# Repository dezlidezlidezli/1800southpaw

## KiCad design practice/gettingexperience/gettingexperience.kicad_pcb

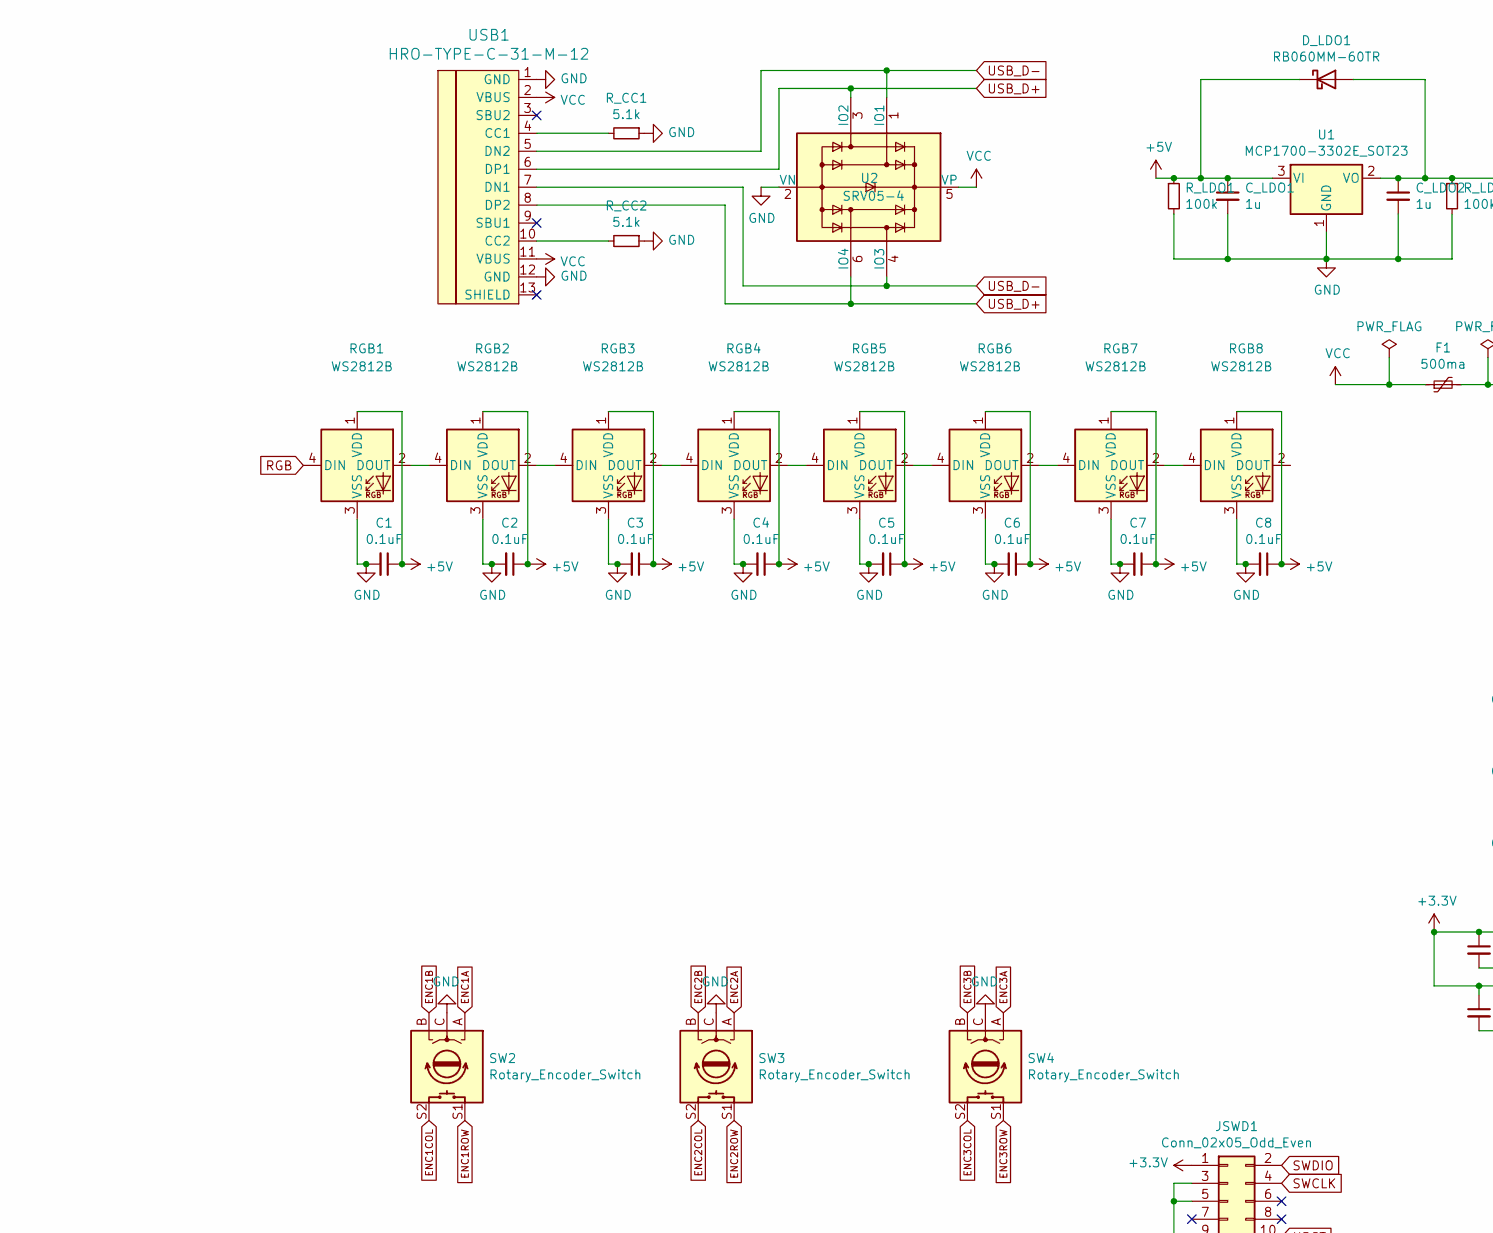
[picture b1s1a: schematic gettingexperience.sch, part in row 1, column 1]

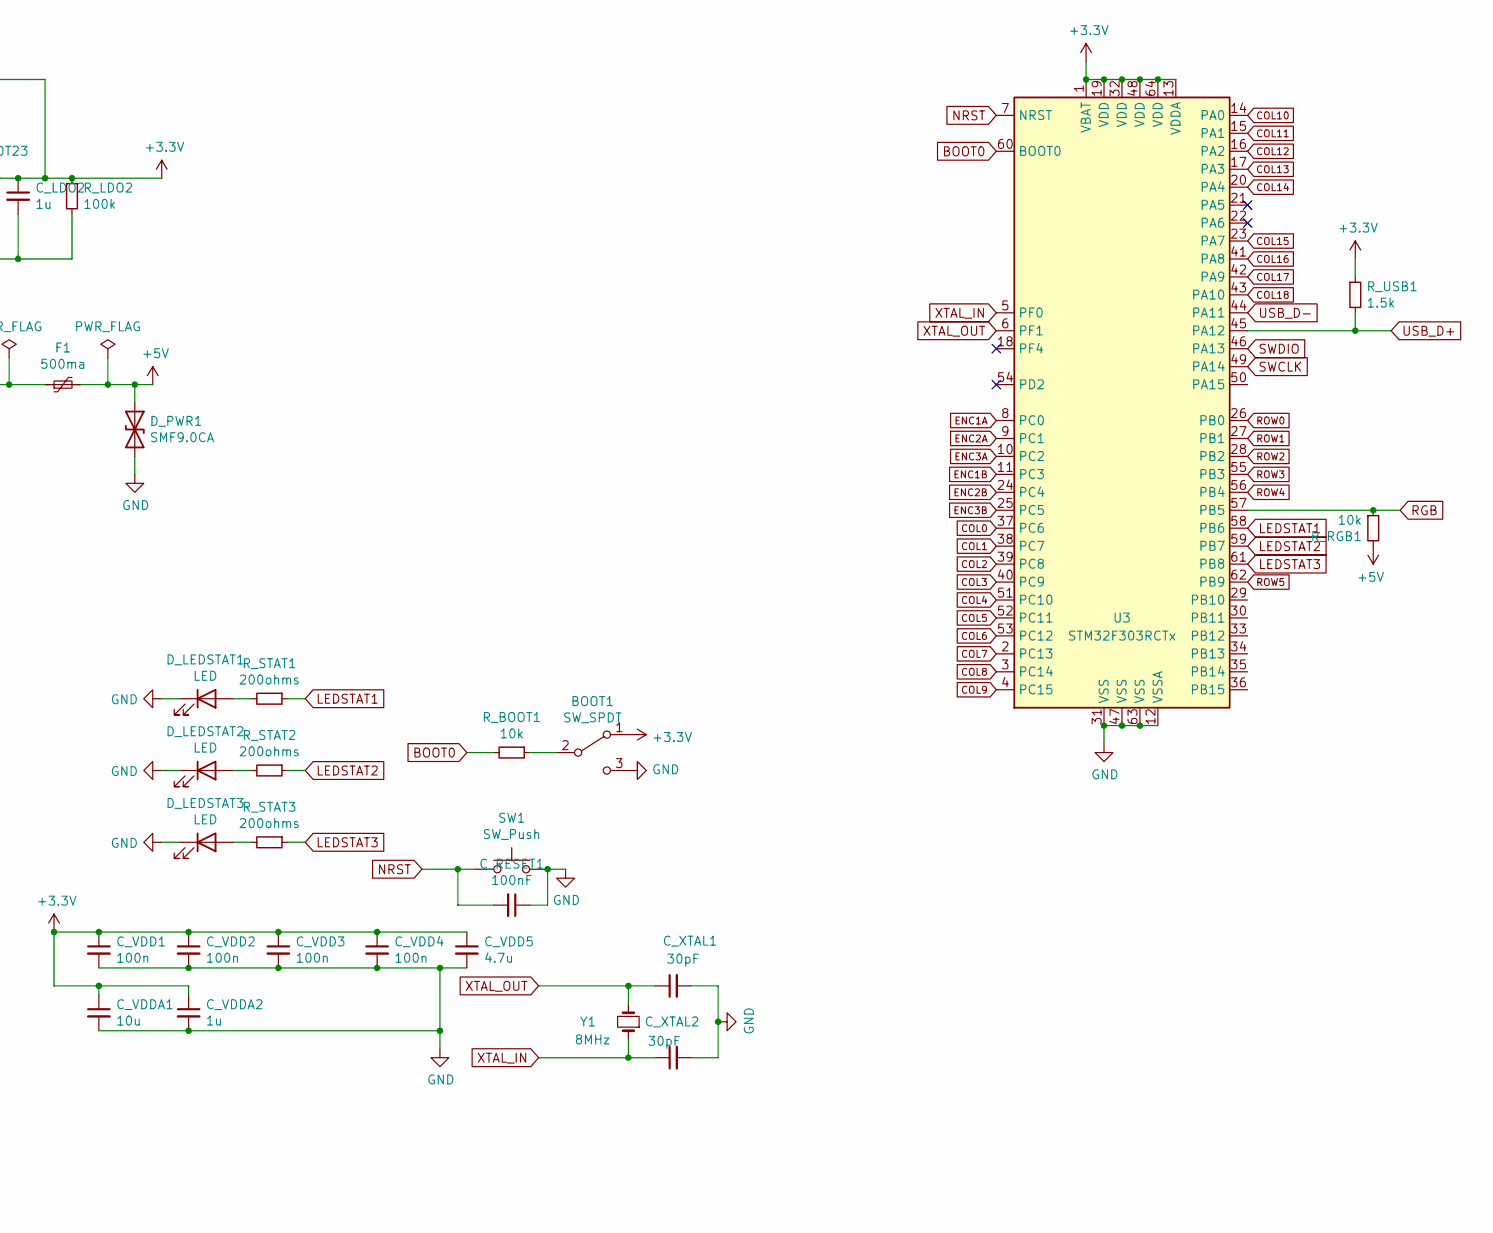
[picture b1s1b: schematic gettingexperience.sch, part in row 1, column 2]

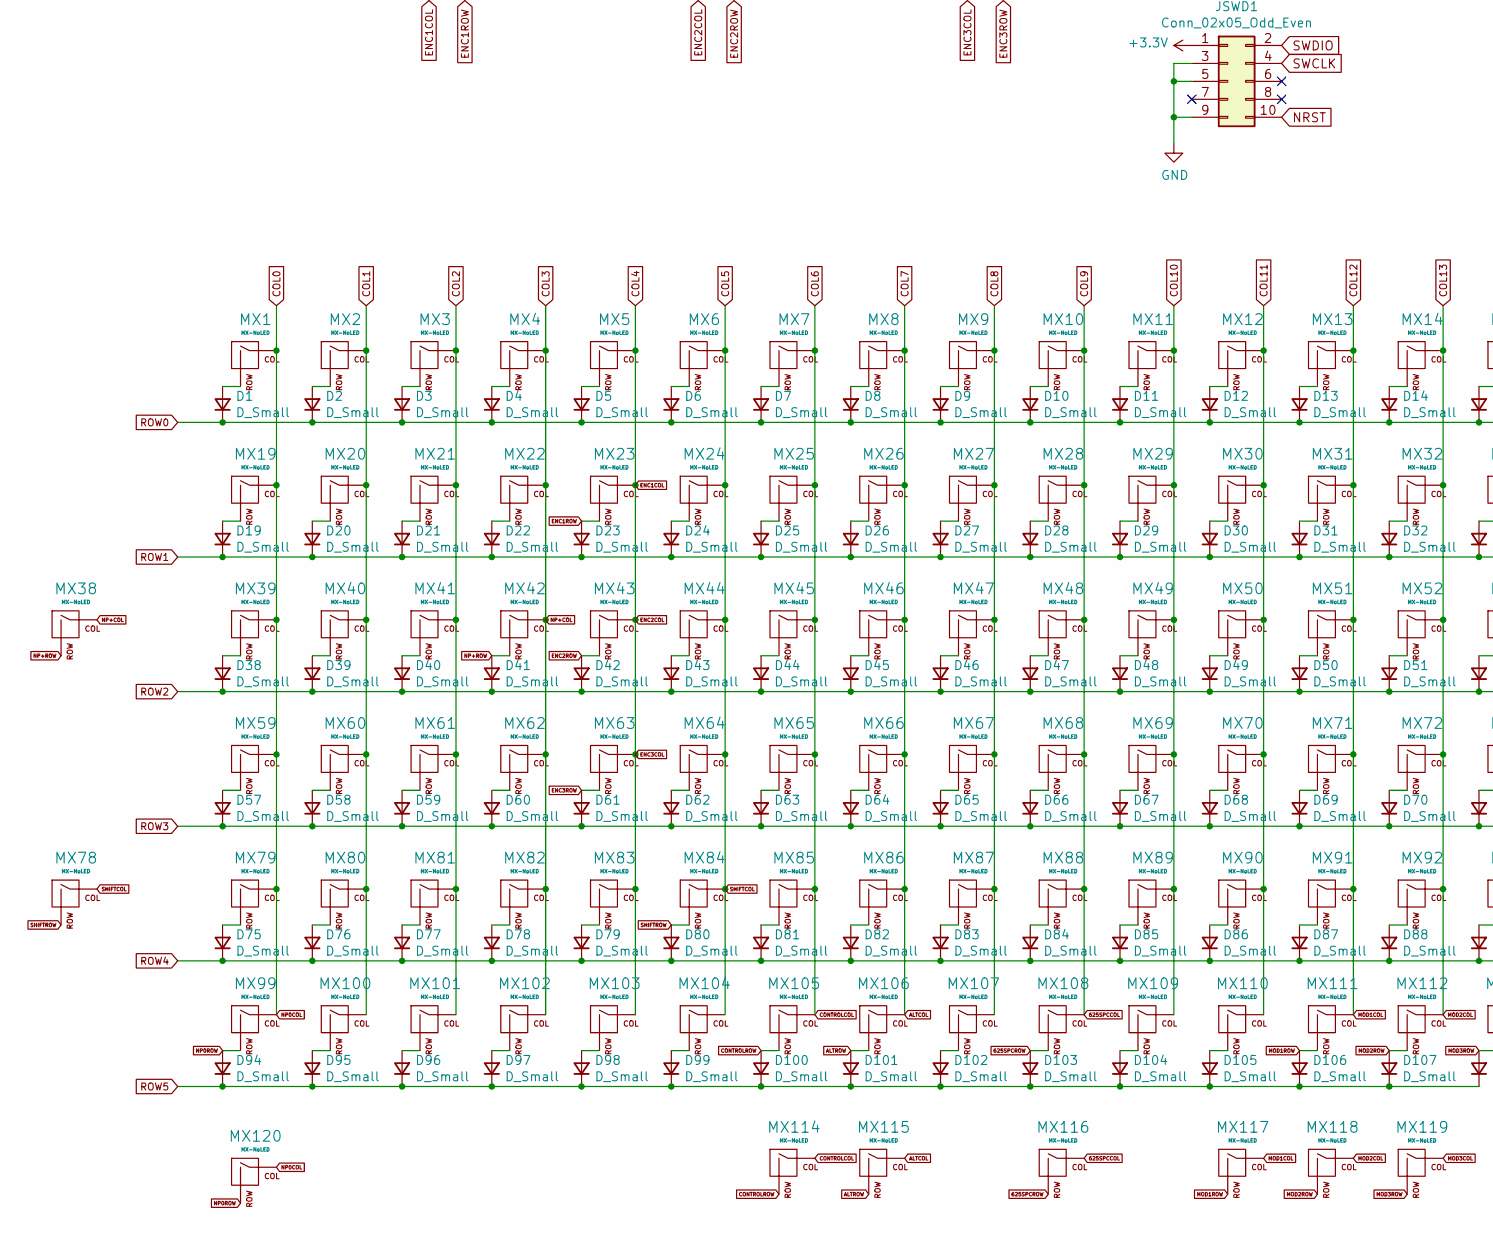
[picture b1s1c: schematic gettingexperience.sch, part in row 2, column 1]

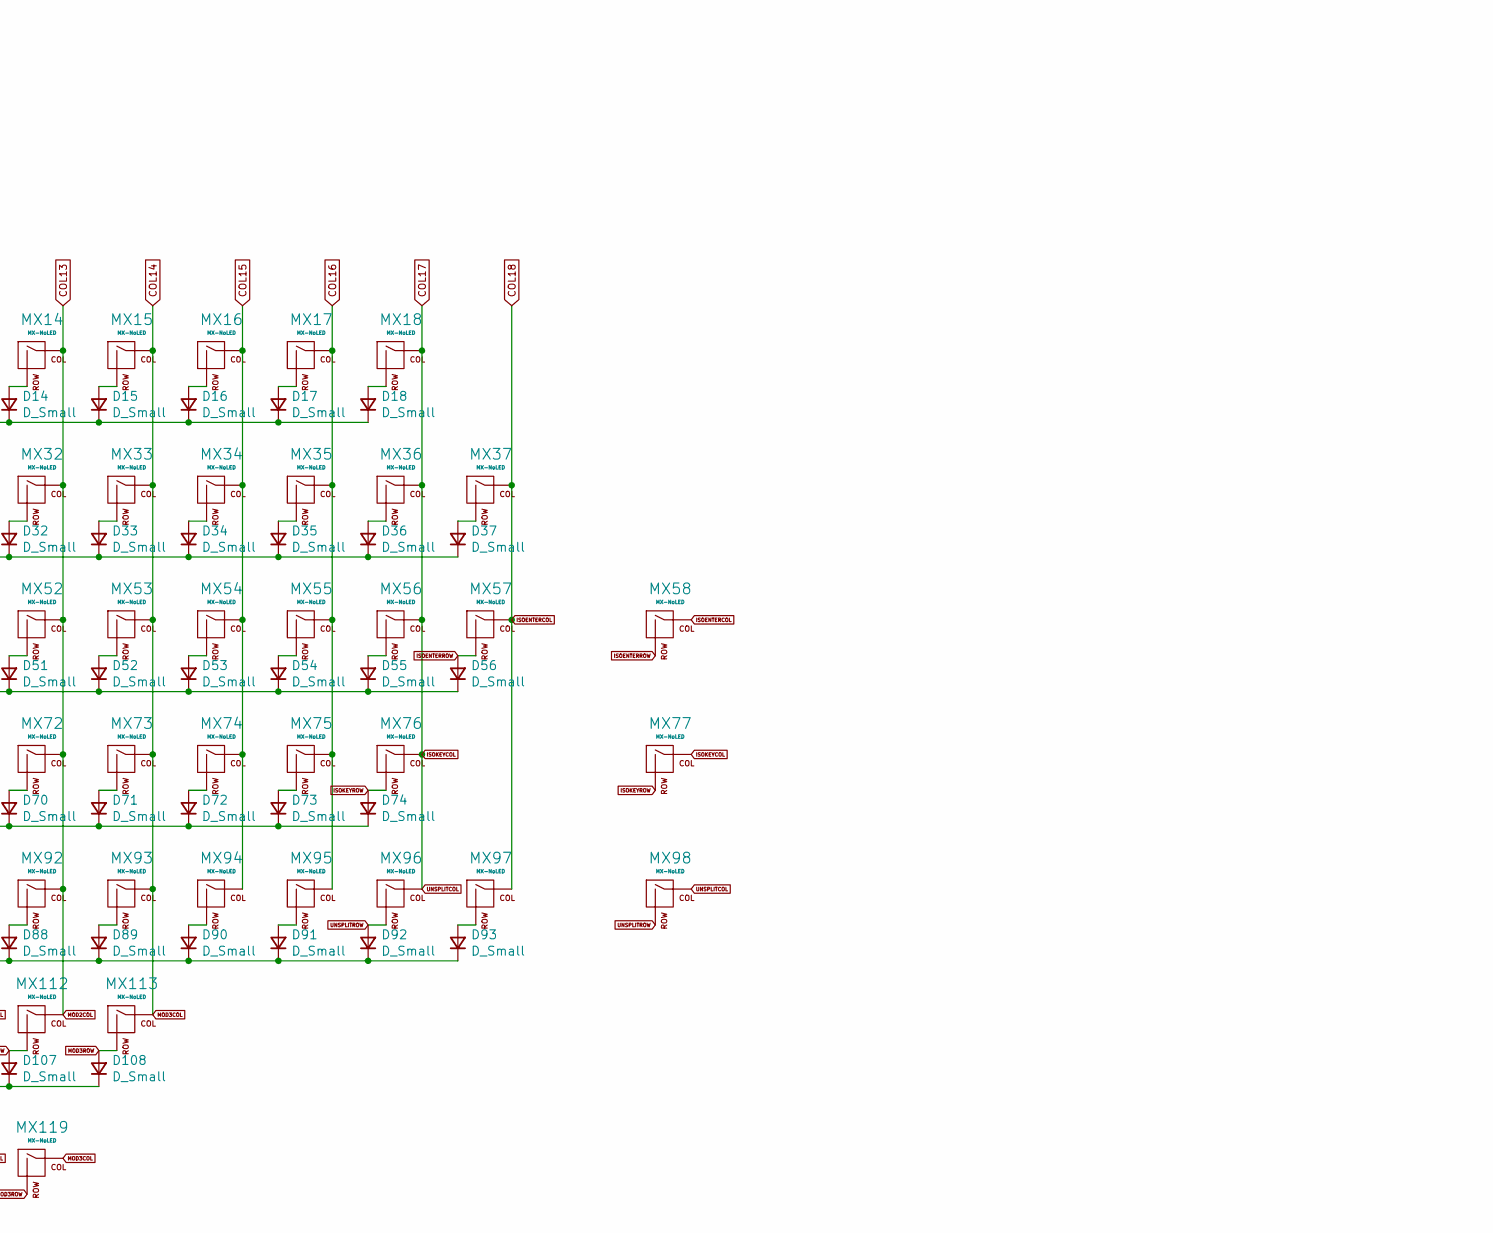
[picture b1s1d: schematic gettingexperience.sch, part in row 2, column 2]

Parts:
BOOT1: SW_SPDT; SW_SPDT_PCM12
C1, C2, C3, C4, C5, C6, C7, C8: 0.1uF; C_0603_1608Metric
C_LDO1, C_LDO2: 1u; C_0603_1608Metric
C_RESET1: 100nF
C_VDD1, C_VDD2, C_VDD3, C_VDD4: 100n; C_0603_1608Metric
C_VDD5: 4.7u; C_0603_1608Metric
C_VDDA1: 10u; C_0603_1608Metric
C_VDDA2: 1u; C_0603_1608Metric
C_XTAL1, C_XTAL2: 30pF; C_0603_1608Metric
D1, D2, D3, D4, D5, D6, D7, D8, D9, D10, D11, D12, D13, D14, D15, D16, D17, D18, D19, D20, D21, D22, D23, D24, D25, D26, D27, D28, D29, D30, D31, D32, D33, D34, D35, D36, D37, D38, D39, D40, D41, D42, D43, D44, D45, D46, D47, D48, D49, D50, D51, D52, D53, D54, D55, D56, D57, D58, D59, D60, D61, D62, D63, D64, D65, D66, D67, D68, D69, D70, D71, D72, D73, D74, D75, D76, D77, D78, D79, D80, D81, D82, D83, D84, D85, D86, D87, D88, D89, D90, D91, D92, D93, D94, D95, D96, D97, D98, D99, D100, D101, D102, D103, D104, D105, D106, D107, D108: D_Small; D_SOD-123
D_LDO1: RB060MM-60TR; D_SOD-123
D_LEDSTAT1, D_LEDSTAT2, D_LEDSTAT3: LED; LED_D5.0mm
D_PWR1: SMF9.0CA; D_SOD-123
F1: 500ma; Fuse_1206_3216Metric
JSWD1: Conn_02x05_Odd_Even; PinHeader_2x05_P2.54mm_Vertical
MX1, MX2, MX3, MX4, MX5, MX6, MX7, MX8, MX9, MX10, MX11, MX12, MX13, MX14, MX15, MX16, MX17, MX18, MX19, MX20, MX21, MX22, MX23, MX24, MX25, MX26, MX27, MX28, MX29, MX30, MX31, MX32, MX33, MX34, MX35, MX36, MX39, MX40, MX41, MX42, MX43, MX45, MX46, MX47, MX48, MX49, MX50, MX51, MX52, MX53, MX54, MX55, MX56, MX59, MX60, MX61, MX62, MX63, MX65, MX66, MX67, MX68, MX69, MX70, MX71, MX72, MX73, MX74, MX75, MX76, MX79, MX80, MX81, MX82, MX83, MX85, MX86, MX87, MX88, MX89, MX90, MX91, MX92, MX93, MX94, MX95, MX97, MX99, MX100, MX101, MX102, MX103, MX104, MX112: MX-NoLED; MXOnly-1U-NoLED
MX37, MX38, MX120: MX-NoLED; MXOnly-2U-NoLED
MX44, MX57, MX105, MX106, MX111, MX113, MX115: MX-NoLED; MXOnly-1.5U-NoLED
MX58: MX-NoLED; MXOnly-ISO-ROTATED-ReversedStabilizers-NoLED
MX64, MX96: MX-NoLED; MXOnly-1.75U-NoLED
MX77, MX78: MX-NoLED; MXOnly-2.25U-NoLED
MX84, MX110, MX114, MX117, MX118, MX119: MX-NoLED; MXOnly-1.25U-NoLED
MX98: MX-NoLED; MXOnly-2.75U-NoLED
MX107, MX109: MX-NoLED; MXOnly-3U-NoLED
MX108: MX-NoLED; MXOnly-7U-NoLED
MX116: MX-NoLED; MXOnly-6.25U-NoLED
RGB1, RGB2, RGB3, RGB4, RGB5, RGB6, RGB7, RGB8: WS2812B; LED_WS2812B_PLCC4_5.0x5.0mm_P3.2mm
R_BOOT1: 10k; R_0603_1608Metric
R_CC1, R_CC2: 5.1k; R_0603_1608Metric
R_LDO1, R_LDO2: 100k; R_0603_1608Metric
R_RGB1: 10k; R_0603_1608Metric
R_STAT1, R_STAT2, R_STAT3: 200ohms; R_0603_1608Metric
R_USB1: 1.5k; R_0603_1608Metric
SW1: SW_Push; SW_SPST_TL3342
SW2, SW3, SW4: Rotary_Encoder_Switch; RotaryEncoder_Alps_EC11E-Switch_Vertical_H20mm
U1: MCP1700-3302E_SOT23; SOT-23
U2: SRV05-4; SOT-23-6
U3: STM32F303RCTx; LQFP-64_10x10mm_P0.5mm
USB1: HRO-TYPE-C-31-M-12; HRO-TYPE-C-31-M-12-HandSoldering
Y1: 8MHz; Crystal_SMD_5032-2Pin_5.0x3.2mm

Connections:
625SPCCOL: MX10.1 (COL), MX28.1 (COL), MX48.1 (COL), MX68.1 (COL), MX88.1 (COL), MX108.1 (COL), MX116.1 (COL), U3.4 (PC15); also elsewhere on the board
625SPCROW: D103.2 (A), MX108.2 (ROW), MX116.2 (ROW)
+3V3: BOOT1.1 (A), C_LDO2.1, C_VDD1.1, C_VDD2.1, C_VDD3.1, C_VDD4.1, C_VDD5.1, C_VDDA1.1, C_VDDA2.1, D_LDO1.2 (A), JSWD1.1, R_LDO2.1, R_USB1.1, U1.2 (VO), U3.1 (VBAT), U3.13 (VDDA), U3.19 (VDD), U3.32 (VDD), U3.48 (VDD), U3.64 (VDD); also elsewhere on the board
+5V: C1.1, C2.1, C3.1, C4.1, C5.1, C6.1, C7.1, C8.1, C_LDO1.1, D_LDO1.1 (K), D_PWR1.1 (A1), F1.2, RGB1.1 (VDD), RGB2.1 (VDD), RGB3.1 (VDD), RGB4.1 (VDD), RGB5.1 (VDD), RGB6.1 (VDD), RGB7.1 (VDD), RGB8.1 (VDD), R_LDO1.1, R_RGB1.2, U1.3 (VI)
ALTCOL: MX8.1 (COL), MX26.1 (COL), MX46.1 (COL), MX66.1 (COL), MX86.1 (COL), MX106.1 (COL), MX115.1 (COL), U3.2 (PC13); also elsewhere on the board
ALTROW: D101.2 (A), MX106.2 (ROW), MX115.2 (ROW)
BOOT0: R_BOOT1.2, U3.60 (BOOT0); also elsewhere on the board
COL0: MX1.1 (COL), MX19.1 (COL), MX39.1 (COL), MX59.1 (COL), MX79.1 (COL), MX99.1 (COL), MX120.1 (COL), U3.37 (PC6); also elsewhere on the board
COL1: MX2.1 (COL), MX20.1 (COL), MX40.1 (COL), MX60.1 (COL), MX80.1 (COL), MX100.1 (COL), U3.38 (PC7); also elsewhere on the board
COL2: MX3.1 (COL), MX21.1 (COL), MX41.1 (COL), MX61.1 (COL), MX81.1 (COL), MX101.1 (COL), U3.39 (PC8); also elsewhere on the board
COL3: MX4.1 (COL), MX22.1 (COL), MX38.1 (COL), MX42.1 (COL), MX62.1 (COL), MX82.1 (COL), MX102.1 (COL), U3.40 (PC9); also elsewhere on the board
COL4: MX5.1 (COL), MX23.1 (COL), MX43.1 (COL), MX63.1 (COL), MX83.1 (COL), MX103.1 (COL), SW2.S2, SW3.S2, SW4.S2, U3.51 (PC10); also elsewhere on the board
COL5: MX6.1 (COL), MX24.1 (COL), MX44.1 (COL), MX64.1 (COL), MX78.1 (COL), MX84.1 (COL), MX104.1 (COL), U3.52 (PC11); also elsewhere on the board
COL6: MX7.1 (COL), MX25.1 (COL), MX45.1 (COL), MX65.1 (COL), MX85.1 (COL), MX105.1 (COL), MX114.1 (COL), U3.53 (PC12); also elsewhere on the board
COL8: MX9.1 (COL), MX27.1 (COL), MX47.1 (COL), MX67.1 (COL), MX87.1 (COL), MX107.1 (COL), U3.3 (PC14); also elsewhere on the board
COL10: MX11.1 (COL), MX29.1 (COL), MX49.1 (COL), MX69.1 (COL), MX89.1 (COL), MX109.1 (COL), U3.14 (PA0); also elsewhere on the board
COL11: MX12.1 (COL), MX30.1 (COL), MX50.1 (COL), MX70.1 (COL), MX90.1 (COL), MX110.1 (COL), U3.15 (PA1); also elsewhere on the board
COL12: MX13.1 (COL), MX31.1 (COL), MX51.1 (COL), MX71.1 (COL), MX91.1 (COL), MX111.1 (COL), MX117.1 (COL), U3.16 (PA2); also elsewhere on the board
COL13: MX14.1 (COL), MX32.1 (COL), MX52.1 (COL), MX72.1 (COL), MX92.1 (COL), MX112.1 (COL), MX118.1 (COL), U3.17 (PA3); also elsewhere on the board
COL14: MX15.1 (COL), MX33.1 (COL), MX53.1 (COL), MX73.1 (COL), MX93.1 (COL), MX113.1 (COL), MX119.1 (COL), U3.20 (PA4); also elsewhere on the board
COL15: MX16.1 (COL), MX34.1 (COL), MX54.1 (COL), MX74.1 (COL), MX94.1 (COL), U3.23 (PA7); also elsewhere on the board
COL16: MX17.1 (COL), MX35.1 (COL), MX55.1 (COL), MX75.1 (COL), MX95.1 (COL), U3.41 (PA8); also elsewhere on the board
COL17: MX18.1 (COL), MX36.1 (COL), MX56.1 (COL), MX76.1 (COL), MX77.1 (COL), MX96.1 (COL), MX98.1 (COL), U3.42 (PA9); also elsewhere on the board
COL18: MX37.1 (COL), MX57.1 (COL), MX58.1 (COL), MX97.1 (COL), U3.43 (PA10); also elsewhere on the board
CONTROLROW: D100.2 (A), MX105.2 (ROW), MX114.2 (ROW)
ENC1A: SW2.A, U3.8 (PC0); also elsewhere on the board
ENC1B: SW2.B, U3.11 (PC3); also elsewhere on the board
ENC1ROW: D23.2 (A), MX23.2 (ROW), SW2.S1
ENC2A: SW3.A, U3.9 (PC1); also elsewhere on the board
ENC2B: SW3.B, U3.24 (PC4); also elsewhere on the board
ENC2ROW: D42.2 (A), MX43.2 (ROW), SW3.S1
ENC3A: SW4.A, U3.10 (PC2); also elsewhere on the board
ENC3B: SW4.B, U3.25 (PC5); also elsewhere on the board
ENC3ROW: D61.2 (A), MX63.2 (ROW), SW4.S1
GND: BOOT1.3 (C), C1.2, C2.2, C3.2, C4.2, C5.2, C6.2, C7.2, C8.2, C_LDO1.2, C_LDO2.2, C_RESET1.1, C_VDD1.2, C_VDD2.2, C_VDD3.2, C_VDD4.2, C_VDD5.2, C_VDDA1.2, C_VDDA2.2, C_XTAL1.2, C_XTAL2.2, D_LEDSTAT1.1 (K), D_LEDSTAT2.1 (K), D_LEDSTAT3.1 (K), D_PWR1.2 (A2), JSWD1.3, JSWD1.5, JSWD1.9, RGB1.3 (VSS), RGB2.3 (VSS), RGB3.3 (VSS), RGB4.3 (VSS), RGB5.3 (VSS), RGB6.3 (VSS), RGB7.3 (VSS), RGB8.3 (VSS), R_CC1.1, R_CC2.1, R_LDO1.2, R_LDO2.2, SW1.2, SW2.C, SW3.C, SW4.C, U1.1 (GND), U2.2 (VN), U3.12 (VSSA), U3.31 (VSS), U3.47 (VSS), U3.63 (VSS), USB1.1 (GND), USB1.12 (GND); also elsewhere on the board
ISOENTERROW: D56.2 (A), MX57.2 (ROW), MX58.2 (ROW)
ISOKEYROW: D74.2 (A), MX76.2 (ROW), MX77.2 (ROW)
LEDSTAT1: R_STAT1.1, U3.58 (PB6); also elsewhere on the board
LEDSTAT2: R_STAT2.1, U3.59 (PB7); also elsewhere on the board
LEDSTAT3: R_STAT3.1, U3.61 (PB8); also elsewhere on the board
MOD1ROW: D106.2 (A), MX111.2 (ROW), MX117.2 (ROW)
MOD2ROW: D107.2 (A), MX112.2 (ROW), MX118.2 (ROW)
MOD3ROW: D108.2 (A), MX113.2 (ROW), MX119.2 (ROW)
NP0ROW: D94.2 (A), MX99.2 (ROW), MX120.2 (ROW)
NP+ROW: D41.2 (A), MX38.2 (ROW), MX42.2 (ROW)
NRST: C_RESET1.2, JSWD1.10, SW1.1, U3.7 (NRST); also elsewhere on the board
unnamed: BOOT1.2 (B), R_BOOT1.1
unnamed: D1.2 (A), MX1.2 (ROW)
unnamed: D2.2 (A), MX2.2 (ROW)
unnamed: D3.2 (A), MX3.2 (ROW)
unnamed: D4.2 (A), MX4.2 (ROW)
unnamed: D5.2 (A), MX5.2 (ROW)
unnamed: D6.2 (A), MX6.2 (ROW)
unnamed: D7.2 (A), MX7.2 (ROW)
unnamed: D8.2 (A), MX8.2 (ROW)
unnamed: D9.2 (A), MX9.2 (ROW)
unnamed: D10.2 (A), MX10.2 (ROW)
unnamed: D11.2 (A), MX11.2 (ROW)
unnamed: D12.2 (A), MX12.2 (ROW)
unnamed: D13.2 (A), MX13.2 (ROW)
unnamed: D14.2 (A), MX14.2 (ROW)
unnamed: D15.2 (A), MX15.2 (ROW)
unnamed: D16.2 (A), MX16.2 (ROW)
unnamed: D17.2 (A), MX17.2 (ROW)
unnamed: D18.2 (A), MX18.2 (ROW)
unnamed: D19.2 (A), MX19.2 (ROW)
unnamed: D20.2 (A), MX20.2 (ROW)
unnamed: D21.2 (A), MX21.2 (ROW)
unnamed: D22.2 (A), MX22.2 (ROW)
unnamed: D24.2 (A), MX24.2 (ROW)
unnamed: D25.2 (A), MX25.2 (ROW)
unnamed: D26.2 (A), MX26.2 (ROW)
unnamed: D27.2 (A), MX27.2 (ROW)
unnamed: D28.2 (A), MX28.2 (ROW)
unnamed: D29.2 (A), MX29.2 (ROW)
unnamed: D30.2 (A), MX30.2 (ROW)
unnamed: D31.2 (A), MX31.2 (ROW)
unnamed: D32.2 (A), MX32.2 (ROW)
unnamed: D33.2 (A), MX33.2 (ROW)
unnamed: D34.2 (A), MX34.2 (ROW)
unnamed: D35.2 (A), MX35.2 (ROW)
unnamed: D36.2 (A), MX36.2 (ROW)
unnamed: D37.2 (A), MX37.2 (ROW)
unnamed: D38.2 (A), MX39.2 (ROW)
unnamed: D39.2 (A), MX40.2 (ROW)
unnamed: D40.2 (A), MX41.2 (ROW)
unnamed: D43.2 (A), MX44.2 (ROW)
unnamed: D44.2 (A), MX45.2 (ROW)
unnamed: D45.2 (A), MX46.2 (ROW)
unnamed: D46.2 (A), MX47.2 (ROW)
unnamed: D47.2 (A), MX48.2 (ROW)
unnamed: D48.2 (A), MX49.2 (ROW)
unnamed: D49.2 (A), MX50.2 (ROW)
unnamed: D50.2 (A), MX51.2 (ROW)
unnamed: D51.2 (A), MX52.2 (ROW)
unnamed: D52.2 (A), MX53.2 (ROW)
unnamed: D53.2 (A), MX54.2 (ROW)
unnamed: D54.2 (A), MX55.2 (ROW)
unnamed: D55.2 (A), MX56.2 (ROW)
unnamed: D57.2 (A), MX59.2 (ROW)
unnamed: D58.2 (A), MX60.2 (ROW)
unnamed: D59.2 (A), MX61.2 (ROW)
unnamed: D60.2 (A), MX62.2 (ROW)
unnamed: D62.2 (A), MX64.2 (ROW)
unnamed: D63.2 (A), MX65.2 (ROW)
unnamed: D64.2 (A), MX66.2 (ROW)
unnamed: D65.2 (A), MX67.2 (ROW)
unnamed: D66.2 (A), MX68.2 (ROW)
unnamed: D67.2 (A), MX69.2 (ROW)
unnamed: D68.2 (A), MX70.2 (ROW)
unnamed: D69.2 (A), MX71.2 (ROW)
unnamed: D70.2 (A), MX72.2 (ROW)
unnamed: D71.2 (A), MX73.2 (ROW)
unnamed: D72.2 (A), MX74.2 (ROW)
unnamed: D73.2 (A), MX75.2 (ROW)
unnamed: D75.2 (A), MX79.2 (ROW)
unnamed: D76.2 (A), MX80.2 (ROW)
unnamed: D77.2 (A), MX81.2 (ROW)
unnamed: D78.2 (A), MX82.2 (ROW)
unnamed: D79.2 (A), MX83.2 (ROW)
unnamed: D81.2 (A), MX85.2 (ROW)
unnamed: D82.2 (A), MX86.2 (ROW)
unnamed: D83.2 (A), MX87.2 (ROW)
unnamed: D84.2 (A), MX88.2 (ROW)
unnamed: D85.2 (A), MX89.2 (ROW)
unnamed: D86.2 (A), MX90.2 (ROW)
unnamed: D87.2 (A), MX91.2 (ROW)
unnamed: D88.2 (A), MX92.2 (ROW)
unnamed: D89.2 (A), MX93.2 (ROW)
unnamed: D90.2 (A), MX94.2 (ROW)
unnamed: D91.2 (A), MX95.2 (ROW)
unnamed: D93.2 (A), MX97.2 (ROW)
unnamed: D95.2 (A), MX100.2 (ROW)
unnamed: D96.2 (A), MX101.2 (ROW)
unnamed: D97.2 (A), MX102.2 (ROW)
unnamed: D98.2 (A), MX103.2 (ROW)
unnamed: D99.2 (A), MX104.2 (ROW)
unnamed: D102.2 (A), MX107.2 (ROW)
unnamed: D104.2 (A), MX109.2 (ROW)
unnamed: D105.2 (A), MX110.2 (ROW)
unnamed: D_LEDSTAT1.2 (A), R_STAT1.2
unnamed: D_LEDSTAT2.2 (A), R_STAT2.2
unnamed: D_LEDSTAT3.2 (A), R_STAT3.2
unnamed: RGB1.2 (DOUT), RGB2.4 (DIN)
unnamed: RGB2.2 (DOUT), RGB3.4 (DIN)
unnamed: RGB3.2 (DOUT), RGB4.4 (DIN)
unnamed: RGB4.2 (DOUT), RGB5.4 (DIN)
unnamed: RGB5.2 (DOUT), RGB6.4 (DIN)
unnamed: RGB6.2 (DOUT), RGB7.4 (DIN)
unnamed: RGB7.2 (DOUT), RGB8.4 (DIN)
unnamed: R_CC1.2, USB1.4 (CC1)
unnamed: R_CC2.2, USB1.10 (CC2)
RGB: RGB1.4 (DIN), R_RGB1.1, U3.57 (PB5); also elsewhere on the board
ROW0: D1.1 (K), D2.1 (K), D3.1 (K), D4.1 (K), D5.1 (K), D6.1 (K), D7.1 (K), D8.1 (K), D9.1 (K), D10.1 (K), D11.1 (K), D12.1 (K), D13.1 (K), D14.1 (K), D15.1 (K), D16.1 (K), D17.1 (K), D18.1 (K), U3.26 (PB0); also elsewhere on the board
ROW1: D19.1 (K), D20.1 (K), D21.1 (K), D22.1 (K), D23.1 (K), D24.1 (K), D25.1 (K), D26.1 (K), D27.1 (K), D28.1 (K), D29.1 (K), D30.1 (K), D31.1 (K), D32.1 (K), D33.1 (K), D34.1 (K), D35.1 (K), D36.1 (K), D37.1 (K), U3.27 (PB1); also elsewhere on the board
ROW2: D38.1 (K), D39.1 (K), D40.1 (K), D41.1 (K), D42.1 (K), D43.1 (K), D44.1 (K), D45.1 (K), D46.1 (K), D47.1 (K), D48.1 (K), D49.1 (K), D50.1 (K), D51.1 (K), D52.1 (K), D53.1 (K), D54.1 (K), D55.1 (K), D56.1 (K), U3.28 (PB2); also elsewhere on the board
ROW3: D57.1 (K), D58.1 (K), D59.1 (K), D60.1 (K), D61.1 (K), D62.1 (K), D63.1 (K), D64.1 (K), D65.1 (K), D66.1 (K), D67.1 (K), D68.1 (K), D69.1 (K), D70.1 (K), D71.1 (K), D72.1 (K), D73.1 (K), D74.1 (K), U3.55 (PB3); also elsewhere on the board
ROW4: D75.1 (K), D76.1 (K), D77.1 (K), D78.1 (K), D79.1 (K), D80.1 (K), D81.1 (K), D82.1 (K), D83.1 (K), D84.1 (K), D85.1 (K), D86.1 (K), D87.1 (K), D88.1 (K), D89.1 (K), D90.1 (K), D91.1 (K), D92.1 (K), D93.1 (K), U3.56 (PB4); also elsewhere on the board
ROW5: D94.1 (K), D95.1 (K), D96.1 (K), D97.1 (K), D98.1 (K), D99.1 (K), D100.1 (K), D101.1 (K), D102.1 (K), D103.1 (K), D104.1 (K), D105.1 (K), D106.1 (K), D107.1 (K), D108.1 (K), U3.62 (PB9); also elsewhere on the board
SHIFTROW: D80.2 (A), MX78.2 (ROW), MX84.2 (ROW)
SWCLK: JSWD1.4, U3.49 (PA14); also elsewhere on the board
SWDIO: JSWD1.2, U3.46 (PA13); also elsewhere on the board
UNSPLITROW: D92.2 (A), MX96.2 (ROW), MX98.2 (ROW)
USB_D+: R_USB1.2, U2.3 (IO2), U2.6 (IO4), U3.45 (PA12), USB1.6 (DP1), USB1.8 (DP2); also elsewhere on the board
USB_D-: U2.1 (IO1), U2.4 (IO3), U3.44 (PA11), USB1.5 (DN2), USB1.7 (DN1); also elsewhere on the board
VCC: F1.1, U2.5 (VP), USB1.2 (VBUS), USB1.11 (VBUS)
XTAL_IN: C_XTAL2.1, U3.5 (PF0), Y1.1; also elsewhere on the board
XTAL_OUT: C_XTAL1.1, U3.6 (PF1), Y1.2; also elsewhere on the board

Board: 2 copper layers, 283 parts (152 on the bottom side), 176 nets, no tracks yet.

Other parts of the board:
C_VDDe: 100n; C_0603_1608Metric
JBREAKOUT1: Conn_01x08_Male; PinHeader_1x08_P2.54mm_Vertical
Ue: STM32F303RCTx; LQFP-64_10x10mm_P0.5mm

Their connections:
625SPCCOL: Ue.4; also elsewhere on the board
+3V3: C_VDDe.1, Ue.1, Ue.13, Ue.19, Ue.32, Ue.48, Ue.64; also elsewhere on the board
ALTCOL: Ue.2; also elsewhere on the board
BOOT0: Ue.60; also elsewhere on the board
BREAKOUT1: JBREAKOUT1.1, Ue.58
BREAKOUT2: JBREAKOUT1.2, Ue.59
BREAKOUT3: JBREAKOUT1.3, Ue.61
BREAKOUT4: JBREAKOUT1.4, Ue.62
BREAKOUT5: JBREAKOUT1.5, Ue.29
BREAKOUT6: JBREAKOUT1.6, Ue.30
BREAKOUT7: JBREAKOUT1.7, Ue.33
BREAKOUT8: JBREAKOUT1.8, Ue.35
COL0: Ue.37; also elsewhere on the board
COL1: Ue.38; also elsewhere on the board
COL2: Ue.39; also elsewhere on the board
COL3: Ue.40; also elsewhere on the board
COL4: Ue.51; also elsewhere on the board
COL5: Ue.52; also elsewhere on the board
COL6: Ue.53; also elsewhere on the board
COL8: Ue.3; also elsewhere on the board
COL10: Ue.14; also elsewhere on the board
COL11: Ue.15; also elsewhere on the board
COL12: Ue.16; also elsewhere on the board
COL13: Ue.17; also elsewhere on the board
COL14: Ue.20; also elsewhere on the board
COL15: Ue.21; also elsewhere on the board
COL16: Ue.22; also elsewhere on the board
COL17: Ue.23; also elsewhere on the board
COL18: Ue.41; also elsewhere on the board
ENC1A: Ue.8; also elsewhere on the board
ENC1B: Ue.11; also elsewhere on the board
ENC2A: Ue.9; also elsewhere on the board
ENC2B: Ue.24; also elsewhere on the board
ENC3A: Ue.10; also elsewhere on the board
ENC3B: Ue.25; also elsewhere on the board
GND: C_VDDe.2, Ue.12, Ue.31, Ue.47, Ue.63; also elsewhere on the board
LEDSTAT1: Ue.42; also elsewhere on the board
LEDSTAT2: Ue.43; also elsewhere on the board
LEDSTAT3: Ue.50; also elsewhere on the board
NRST: Ue.7; also elsewhere on the board
RGB: Ue.36; also elsewhere on the board
ROW0: Ue.26; also elsewhere on the board
ROW1: Ue.27; also elsewhere on the board
ROW2: Ue.28; also elsewhere on the board
ROW3: Ue.55; also elsewhere on the board
ROW4: Ue.56; also elsewhere on the board
ROW5: Ue.57; also elsewhere on the board
SWCLK: Ue.49; also elsewhere on the board
SWDIO: Ue.46; also elsewhere on the board
USB_D+: Ue.45; also elsewhere on the board
USB_D-: Ue.44; also elsewhere on the board
XTAL_IN: Ue.5; also elsewhere on the board
XTAL_OUT: Ue.6; also elsewhere on the board

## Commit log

2020-11-07 second commit
2020-11-08 commit for check
